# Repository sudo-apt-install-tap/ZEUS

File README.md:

# ZEUS: A One Handed Keeb Made For Speed
**No extra keys. Only essentials. Built for speed, precision, and one-handed precession.**

## Why ZEUS?
Zeus has a custom layout designed for speed and efficiency. This is based on a generic one handed gaming board.. yeah the kind you get on alibaba. BUT!! the diffrence is instead of keys numeric or function keys it has all alphabet keys. This make it perfect for speed typists.

## How Do I Flash ZEUS?
WHY WOULD YOU WANNA FLASH A GOD WHO HAS A HISTORY OF ADULTRY AND CREATING DEMIGODS. /j
But in all seriousness you just need to get the firmware and then just flash the code through any ide.

## RENDER

## PCB

## Schematic

## BOM
### *not a bomb a BOM, Bill Of Materials*

| ID | Component | Qty | Designation | Supplier | Unit (INR) | Total (INR) |
|----|----------|-----|-------------|----------|------------|-------------|
| 1 | Diode SMD 123 | 36 | 1N4148WT | [Robu](https://robu.in/product/tpmbr140sft1g-tech-public-sod-123-schottky-diodes-rohs/) | ₹2.49 | ₹89.64 |
| 2 | Switches (Pack of 10) | 4 | SW_Push | [StacksKB](https://stackskb.com/store/click-inc-hp-switch-pack-of-10-pre-order/) | ₹180.00 | ₹720.00 |
| 3 | Raspberry Pi Pico W | 1 | RaspberryPi_Pico_W | [Robu](https://robu.in/product/raspberry-pi-pico-w/) | ₹614.00 | ₹614.00 |
| 4 | Keycaps | 1 | — | [StacksKB](https://stackskb.com/store/veekos-gradient-keycaps-cherry-profile-135-keys/) | ₹1,299.00 | ₹1,299.00 |
| 5 | Hotswap Sockets | 34 | SW_Push | [StacksKB](https://stackskb.com/store/ttc-pokayoke-hotswap-sockets-v2-10000-cycles) | ₹10.00 | ₹340.00 |
| 6 | PCB Fabrication | 1 | — | [JLCPCB](https://cart.jlcpcb.com/shopcart/cart) | ₹2,294.11 | ₹2,294.11 |

---

### 💸 Cost Summary

- **Total (INR): ₹5,356.75**
- **Total (USD): ~$59.34**
- **Additional Cost [Case + Plate] (USD): $40**
- **Rounded:** **$100**

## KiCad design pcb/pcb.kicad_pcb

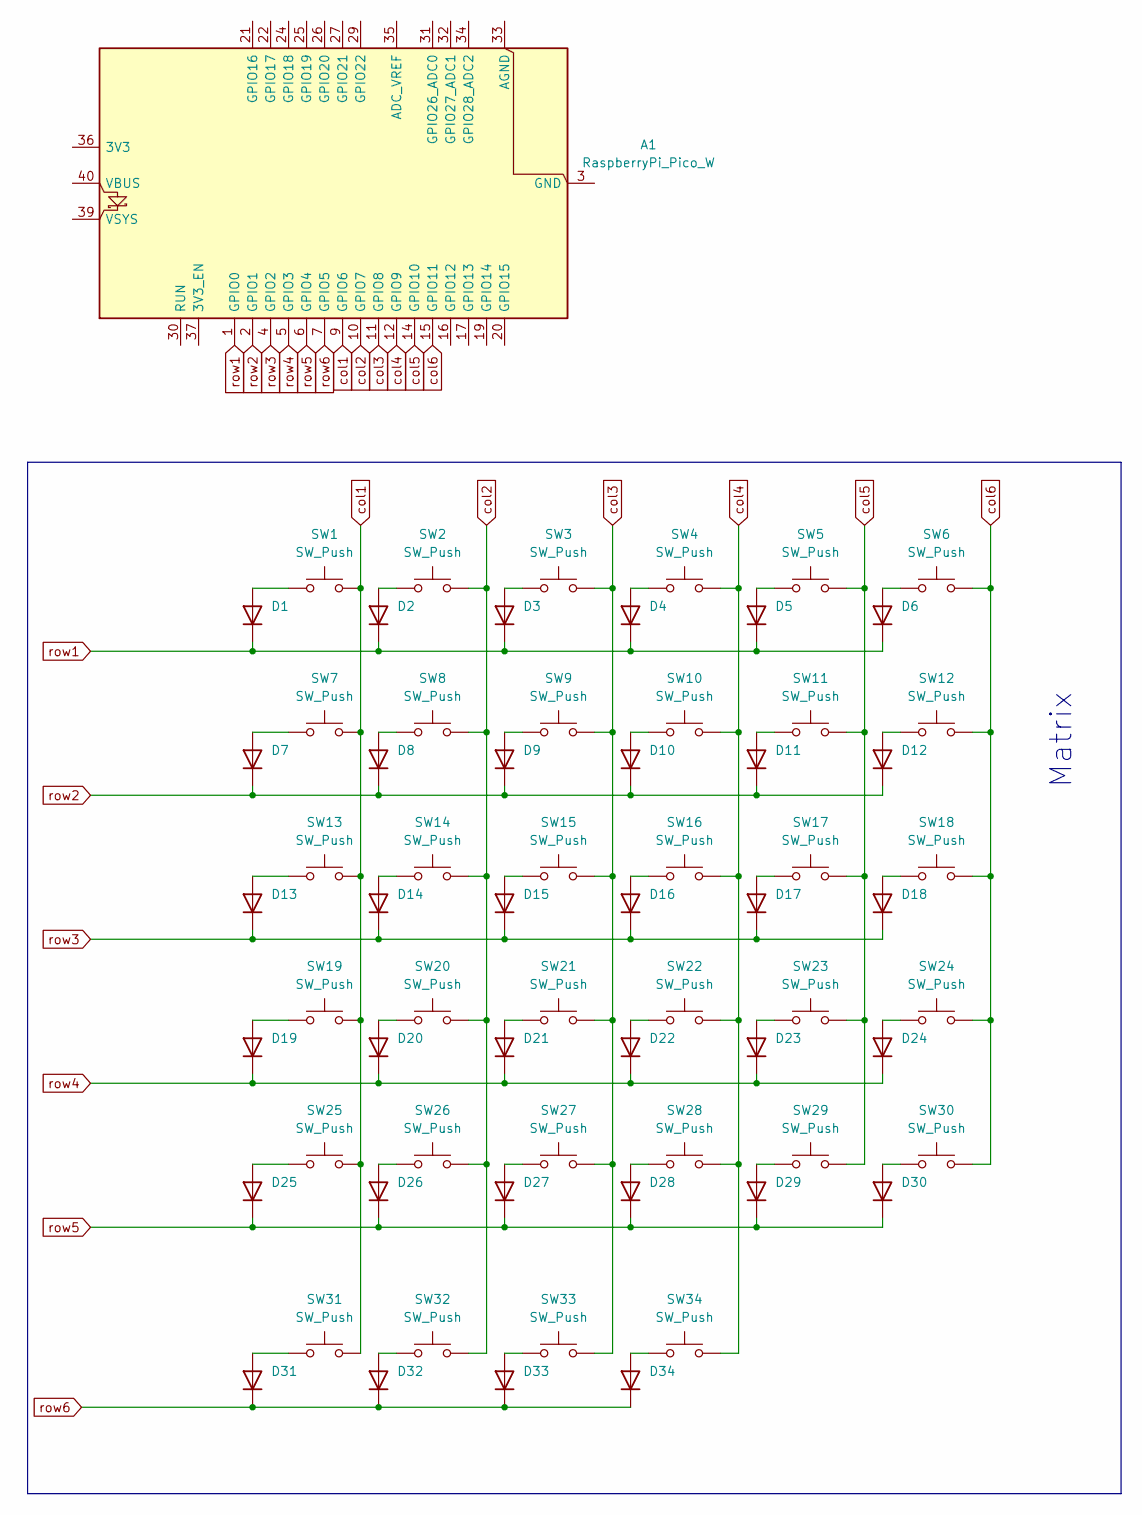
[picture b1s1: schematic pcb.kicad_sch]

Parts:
A1: RaspberryPi_Pico_W; RaspberryPi_Pico_W_SMD_HandSolder
D1, D2, D3, D4, D5, D6, D7, D8, D9, D10, D11, D12, D13, D14, D15, D16, D17, D18, D19, D20, D21, D22, D23, D24, D25, D26, D27, D28, D29, D30, D31, D32, D33, D34: 1N4148WT; D_SOD-523
SW1, SW2, SW3, SW4, SW5, SW6, SW7, SW8, SW9, SW10, SW11, SW12, SW13, SW14, SW15, SW16, SW17, SW18, SW19, SW20, SW21, SW22, SW23, SW24, SW25, SW26, SW27, SW28, SW29, SW30, SW31, SW32, SW33, SW34: SW_Push; SW_Cherry_MX_1.00u_PCB

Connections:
unnamed: A1.3 (GND), A1.8 (GND), A1.13 (GND), A1.18 (GND), A1.23 (GND), A1.28 (GND), A1.38 (GND)
unnamed: D1.2 (A), SW1.1
unnamed: D2.2 (A), SW2.1
unnamed: D3.2 (A), SW3.1
unnamed: D4.2 (A), SW4.1
unnamed: D5.2 (A), SW5.1
unnamed: D6.2 (A), SW6.1
unnamed: D7.2 (A), SW7.1
unnamed: D8.2 (A), SW8.1
unnamed: D9.2 (A), SW9.1
unnamed: D10.2 (A), SW10.1
unnamed: D11.2 (A), SW11.1
unnamed: D12.2 (A), SW12.1
unnamed: D13.2 (A), SW13.1
unnamed: D14.2 (A), SW14.1
unnamed: D15.2 (A), SW15.1
unnamed: D16.2 (A), SW16.1
unnamed: D17.2 (A), SW17.1
unnamed: D18.2 (A), SW18.1
unnamed: D19.2 (A), SW19.1
unnamed: D20.2 (A), SW20.1
unnamed: D21.2 (A), SW21.1
unnamed: D22.2 (A), SW22.1
unnamed: D23.2 (A), SW23.1
unnamed: D24.2 (A), SW24.1
unnamed: D25.2 (A), SW25.1
unnamed: D26.2 (A), SW26.1
unnamed: D27.2 (A), SW27.1
unnamed: D28.2 (A), SW28.1
unnamed: D29.2 (A), SW29.1
unnamed: D30.2 (A), SW30.1
unnamed: D31.2 (A), SW31.1
unnamed: D32.2 (A), SW32.1
unnamed: D33.2 (A), SW33.1
unnamed: D34.2 (A), SW34.1
col1: A1.9 (GPIO6), SW1.2, SW7.2, SW13.2, SW19.2, SW25.2, SW31.2
col2: A1.10 (GPIO7), SW2.2, SW8.2, SW14.2, SW20.2, SW26.2, SW32.2
col3: A1.11 (GPIO8), SW3.2, SW9.2, SW15.2, SW21.2, SW27.2, SW33.2
col4: A1.12 (GPIO9), SW4.2, SW10.2, SW16.2, SW22.2, SW28.2, SW34.2
col5: A1.14 (GPIO10), SW5.2, SW11.2, SW17.2, SW23.2, SW29.2
col6: A1.15 (GPIO11), SW6.2, SW12.2, SW18.2, SW24.2, SW30.2
row1: A1.1 (GPIO0), D1.1 (K), D2.1 (K), D3.1 (K), D4.1 (K), D5.1 (K), D6.1 (K)
row2: A1.2 (GPIO1), D7.1 (K), D8.1 (K), D9.1 (K), D10.1 (K), D11.1 (K), D12.1 (K)
row3: A1.4 (GPIO2), D13.1 (K), D14.1 (K), D15.1 (K), D16.1 (K), D17.1 (K), D18.1 (K)
row4: A1.5 (GPIO3), D19.1 (K), D20.1 (K), D21.1 (K), D22.1 (K), D23.1 (K), D24.1 (K)
row5: A1.6 (GPIO4), D25.1 (K), D26.1 (K), D27.1 (K), D28.1 (K), D29.1 (K), D30.1 (K)
row6: A1.7 (GPIO5), D31.1 (K), D32.1 (K), D33.1 (K), D34.1 (K)

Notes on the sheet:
Matrix

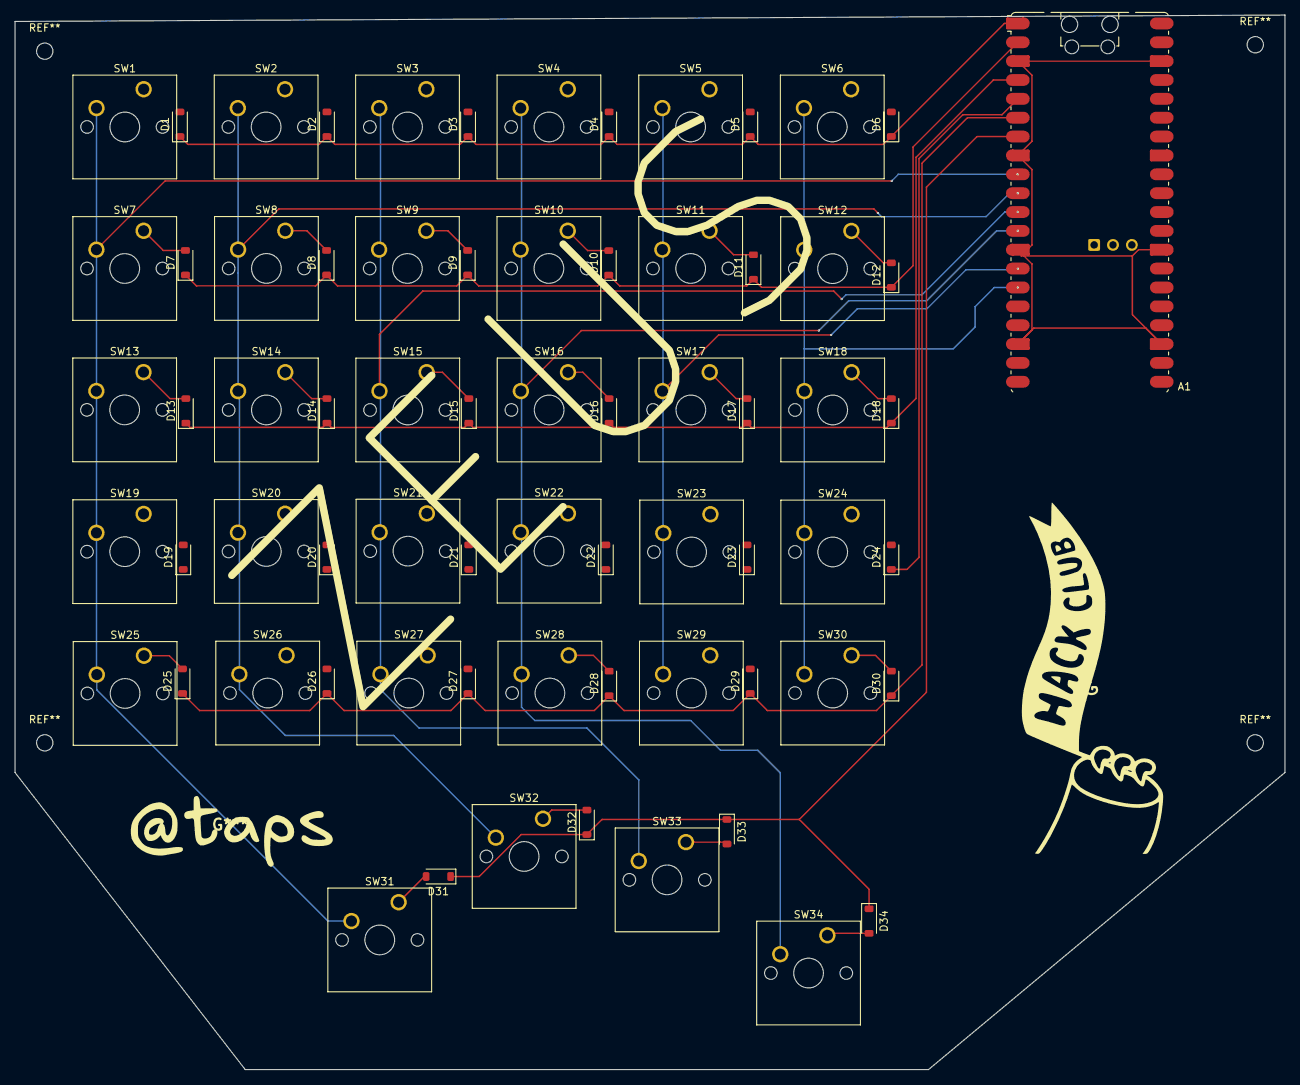
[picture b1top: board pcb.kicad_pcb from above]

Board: 2 copper layers, 171.0 x 142.0 mm, 69 parts (0 on the bottom side), 47 nets.

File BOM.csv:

Id,Name,Quantity,Designation,Supplier and ref,Price Per Unit INR,Total INR
1,Diode SMD 123,36,1N4148WT,https://robu.in/product/tpmbr140sft1g-tech-public-sod-123-sc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,₹2.49,₹89.64
2,Switches (Pack of 10),4,SW_Push,https://stackskb.com/store/click-inc-hp-switch-pack-of-10-pr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,₹180.00,₹720.00
3,RaspberryPi Pico W,1,RaspberryPi_Pico_W,https://robu.in/product/raspberry-pi-pico-w/,₹614.00,₹614.00
4,Keycaps,1,,https://stackskb.com/store/veekos-gradient-keycaps-cherry-pr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,"₹1,299.00","₹1,299.00"
5,Hotswap Sockets(Pack of 1),34,SW_Push,https://stackskb.com/store/ttc-pokayoke-hotswap-sockets-v2-1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,₹10.00,₹340.00
6,PCB Fab,1,,https://cart.jlcpcb.com/shopcart/cart,"₹2,294.11","₹2,294.11"
,,,,TOTAL,,"₹5,356.75"
,,,,TOTAL USD,,$59.34
,,,,Round off,,$60

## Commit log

2026-01-10 Add ZEUS keyboard details to README
    Added detailed information about ZEUS keyboard including layout, flashing instructions, images, and BOM.
2026-01-10 Modify BOM section header formatting
    Updated BOM section header to include HTML line break.
2026-01-21 Add additional images to README
2026-01-21 Update cost summary with additional costs
2026-01-28 Update README with BOM section and images
2026-01-28 Enhance README with details about ZEUS keyboard
    Updated the README with additional information about ZEUS, including its layout, flashing instructions, and PCB images.
2026-01-28 Updated Images with cart
